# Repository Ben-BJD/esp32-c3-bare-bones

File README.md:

# ESP32-C3 - Bare Bones DevKitM - KiCAD Source Files

This project is a work in progress.

## Goal: 

Create a simplified custom PCB based on the [ESP32-C3-DevKitM-1](https://docs.espressif.com/projects/esp-dev-kits/en/latest/esp32c3/esp32-c3-devkitm-1/user_guide.html)

This board is designed to consume as little power as possible while in deep sleep. Ideally 5uF as per the ESP-32 [datasheet](https://www.espressif.com/sites/default/files/documentation/esp32-c3-mini-1_datasheet_en.pdf). To this end the Voltage Regulator, RGB LED, Power LED and USB-UART interface have been removed. Leaving just the MCU, Reset/Boot button and header pins.

The board will need to be powered directly with a power source between 3.0 and 3.6v. It is important that the voltage never exceed 3.6v. Regular Lipo batteries typically have a maximum voltage of 4.2v so are not suitable.

This board was designed to be powered by a 3.2v LiFePO4 battery. LiFePO4 batteries can reach 3.65v when fully charged. A BMS set to cut off at 3.6V or slightly lower will be necesary.

The board will need to be programmed with an FDTI programmer as there is no USB interface.

## Resources:

* [ESP32-C3-MINI-1 MCU Datasheet](https://www.espressif.com/sites/default/files/documentation/esp32-c3-mini-1_datasheet_en.pdf)
* [ESP32-C3-DevKitM-1 Docs](https://docs.espressif.com/projects/esp-dev-kits/en/latest/esp32c3/esp32-c3-devkitm-1/user_guide.html)
* [ESP32-C3-DevKitM-1 Schematic](https://dl.espressif.com/dl/schematics/SCH_ESP32-C3-DEVKITM-1_V1_20200915A.pdf)

## Schematic:

[PDF Version](esp32-c3-bare-bones-schematic.pdf)

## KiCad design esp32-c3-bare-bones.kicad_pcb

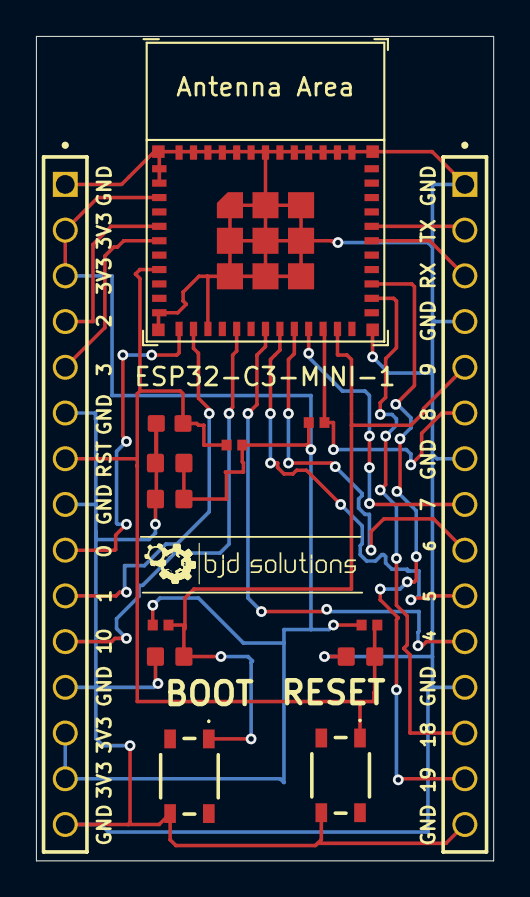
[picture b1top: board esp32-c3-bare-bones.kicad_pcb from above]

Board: 2 copper layers, 25.4 x 45.8 mm, 14 parts (0 on the bottom side), 18 nets.

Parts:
BOOT: SKRPARE010
C1: 1uF 16V 10%; CAPC1608X90N
C2, C4, C5: 0.1uF 50V 10%; CAPC1608X100N
C3: 10uF 25V 20%; CAPC1608X100N
ESP32-C3-MINI-1: ESP32-C3-MINI-1
J1, J2: ESW-115-44-G-S; SAMTEC_ESW-115-44-G-S
R1, R2, R3, R4: 10k 1%; RESC1005X37N
RESET: SKRPARE010

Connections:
CHIP_PU: C1.2, C5.2, ESP32-C3-MINI-1.8 (EN/CHIP_PU), J1.07, R1.1, R3.2, RESET.1
GND: BOOT.4, C1.1, C2.1, C3.1, C4.1, C5.1, ESP32-C3-MINI-1.1 (GND), ESP32-C3-MINI-1.2 (GND), ESP32-C3-MINI-1.11 (GND), ESP32-C3-MINI-1.14 (GND), ESP32-C3-MINI-1.36 (GND), ESP32-C3-MINI-1.37 (GND), ESP32-C3-MINI-1.38 (GND), ESP32-C3-MINI-1.39 (GND), ESP32-C3-MINI-1.40 (GND), ESP32-C3-MINI-1.41 (GND), ESP32-C3-MINI-1.42 (GND), ESP32-C3-MINI-1.43 (GND), ESP32-C3-MINI-1.44 (GND), ESP32-C3-MINI-1.45 (GND), ESP32-C3-MINI-1.46 (GND), ESP32-C3-MINI-1.47 (GND), ESP32-C3-MINI-1.48 (GND), ESP32-C3-MINI-1.49 (GND), ESP32-C3-MINI-1.50 (GND), ESP32-C3-MINI-1.51 (GND), ESP32-C3-MINI-1.52 (GND), ESP32-C3-MINI-1.53 (GND), J1.01, J1.06, J1.08, J1.12, J1.15, J2.01, J2.04, J2.07, J2.12, J2.15, RESET.4
GPIO0: ESP32-C3-MINI-1.12 (GPIO0/ADC1_CH0/XTAL_32K_P), J1.09
GPIO1: ESP32-C3-MINI-1.13 (GPIO1/ADC1_CH1/XTAL_32K_N), J1.10
GPIO2: ESP32-C3-MINI-1.5 (GPIO2/ADC1_CH2), J1.04
GPIO3: ESP32-C3-MINI-1.6 (GPIO3/ADC1_CH3), J1.05
GPIO4: ESP32-C3-MINI-1.18 (GPIO4/ADC1_CH4), J2.11
GPIO5: ESP32-C3-MINI-1.19 (GPIO5/ADC2_CH0), J2.10
GPIO6: ESP32-C3-MINI-1.20 (GPIO6), J2.09
GPIO7: ESP32-C3-MINI-1.21 (GPIO7), J2.08
GPIO8: ESP32-C3-MINI-1.22 (GPIO8), J2.06, R4.2
GPIO9: BOOT.1, C4.2, ESP32-C3-MINI-1.23 (GPIO9), J2.05, R2.2
GPIO10: ESP32-C3-MINI-1.16 (GPIO10), J1.11
GPIO18: ESP32-C3-MINI-1.26 (GPIO18/USB_D-), J2.13
GPIO19: ESP32-C3-MINI-1.27 (GPIO19/USB_D+), J2.14
U0RXD: ESP32-C3-MINI-1.30 (GPIO20/U0RXD), J2.03
U0TXD: ESP32-C3-MINI-1.31 (GPIO21/U0TXD), J2.02
VCC_3V3: C2.2, C3.2, ESP32-C3-MINI-1.3 (3V3), J1.02, J1.03, J1.13, J1.14, R1.2, R2.1, R3.1, R4.1

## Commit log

2025-10-12 Initial
2025-10-12 Add Readme
2025-10-16 PCB Design
